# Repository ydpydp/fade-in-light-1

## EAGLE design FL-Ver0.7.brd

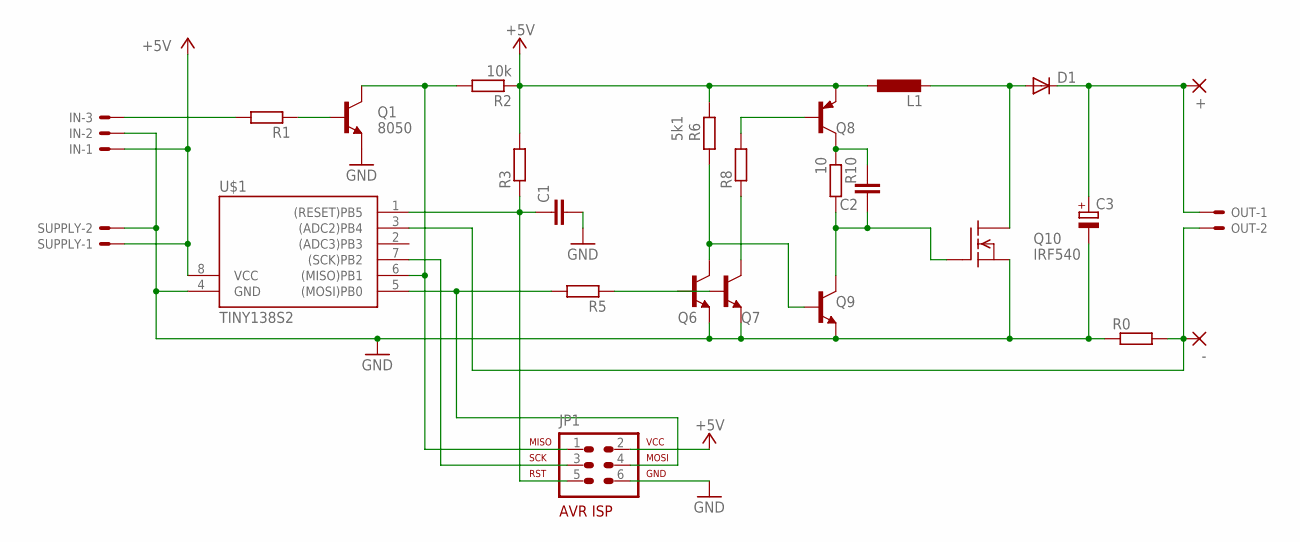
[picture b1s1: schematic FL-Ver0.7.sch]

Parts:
+: 1,6/0,9
-: 1,6/0,9
C1, C2: C-EUC0805; C0805
C3: CPOL-EU153CLV-0807; 153CLV-0807
D1: DIODE-SMB; SMB
IN: 22-23-2031
JP1: AVR-ISP-6VERT; AVR-ISP-6
L1: DO3316P
OUT: 22-23-2021
Q1: 8050; SOT23-BEC
Q6, Q7, Q9: SS8050SMDSMD; SOT23-BEC
Q8: SS8550SMDSMD; SOT23-BEC
Q10: IRF540; TO220
R0: R-EU_0613/15; P0613/15
R1, R3, R5, R8: R-EU_M0805; M0805
R2: 10k; M0805
R6: 5k1; M0805
R10: 10; M0805
SUPPLY: 22-23-2021
U$1: TINY138S2; SO08

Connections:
+5V: IN.1, JP1.2, L1.2, Q8.E, R2.1, R3.2, R6.2, SUPPLY.1, U$1.8 (VCC)
FET-D: D1.A, L1.1, Q10.2 (D)
GND: C1.2, C3.-, IN.2, JP1.6, Q1.E, Q6.E, Q7.E, Q9.E, Q10.3 (S), R0.1, SUPPLY.2, U$1.4 (GND)
unnamed: Q6.C, Q9.B, R6.1
unnamed: JP1.3, U$1.7 ((SCK)PB2)
unnamed: Q6.B, Q7.B, R5.1
unnamed: C1.1, JP1.5, R3.1, U$1.1 ((RESET)PB5)
unnamed: Q8.B, R8.2
unnamed: C2.2, Q8.C, R10.1
unnamed: C2.1, Q9.C, Q10.1 (G), R10.2
unnamed: Q1.B, R1.1
unnamed: IN.3, R1.2
unnamed: +.1, C3.+, D1.C, OUT.1
unnamed: JP1.4, R5.2, U$1.5 ((MOSI)PB0)
unnamed: JP1.1, Q1.C, R2.2, U$1.6 ((MISO)PB1)
unnamed: -.1, OUT.2, R0.2, U$1.3 ((ADC2)PB4)
unnamed: Q7.C, R8.1

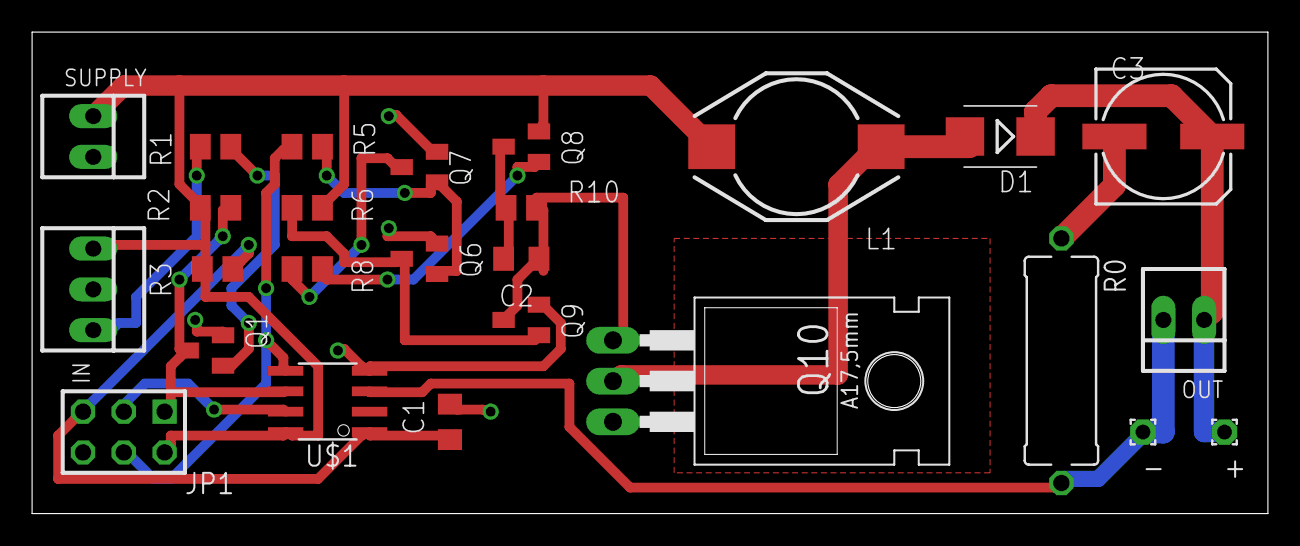
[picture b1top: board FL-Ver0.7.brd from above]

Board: 2 copper layers, 77.0 x 30.0 mm, 26 parts (0 on the bottom side), 17 nets.

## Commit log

2013-09-29 2013-09-29 first use git hub manage eagle files
    没什么,开始使用
2013-09-29 2013-09-30
    設計印製板
